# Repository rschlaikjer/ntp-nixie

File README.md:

# Nixie-NTP

### Nixie clock with NTP synchronisation

Like every amateur electrical engineer, I felt the need to make my own nixie
clock. However, I decided to add a bit of modern day tech and have the clock
set itself over NTP instead of requiring the user to manually adjust buttons.

The schematics provided detail the two boards - one control (arduino, ethernet)
and one display (shift registers, high voltage transistors).

## Partlist
#### (Digikey P/N in parens)

**Logic:**

- Atmega 328P (ATMEGA328-PU-ND / $3.01)
- Silvertel A9700 PoE module (N/A / $10)
- ENC28J60 ethernet PHY (ENC28J60-I/SO-ND / $2.83)
- RB1-125BHQ1A RJ45 jack with magnetics (N/A / $3.00)
- LM1117 3.3V regulator (LM1117T-3.3/NOPB-ND / $1.49)

**12-200V DC Boost:**
- 0.1uF 250V film cap (PCF1412CT-ND / $2.25)
- 4.7uF 450V alum cap (493-6196-1-ND / $1.51)
- MAX1771 DC-DC switching controller (MAX1771EPA+-ND / $7.23)
- 250V MOSFET (IRF644PBF-ND / $1.23)
- 100uF 20V tantalum cap (478-1746-1-ND / $2.52)
- 0.1uF 25V ceramic cap (490-1726-1-ND / $0.05)
- 10uF 25V tantalum cap (478-1762-1-ND / $1.02)
- 300V diode (ES2F-E3/52TGICT-ND / $0.40)
- 10k resistor (311-10.0KCRCT-ND / $0.02)
- 100uH inductor (M8603CT-ND / $0.81)
- 1.5M resistor (PT1.5MXCT-ND / $0.80)
- 0.05 ohm resistor (P50MCT-ND / $1.14)
- 5k trimmer pot (3214W-502ECT-ND / $3.18)

**Display Board**

- LS595 shift register with latch (296-1600-5-ND, $0.62)
- MPSA42 (or similar) high voltage transistors (MPSA42FS-ND, $0.22)
- Nixie tubes (Eagle footprint designed around the IN-14, YMMV)
- 1k resistors for regulating transistor base current
- 15k resistors for limiting nixie current

## Pretty pictures

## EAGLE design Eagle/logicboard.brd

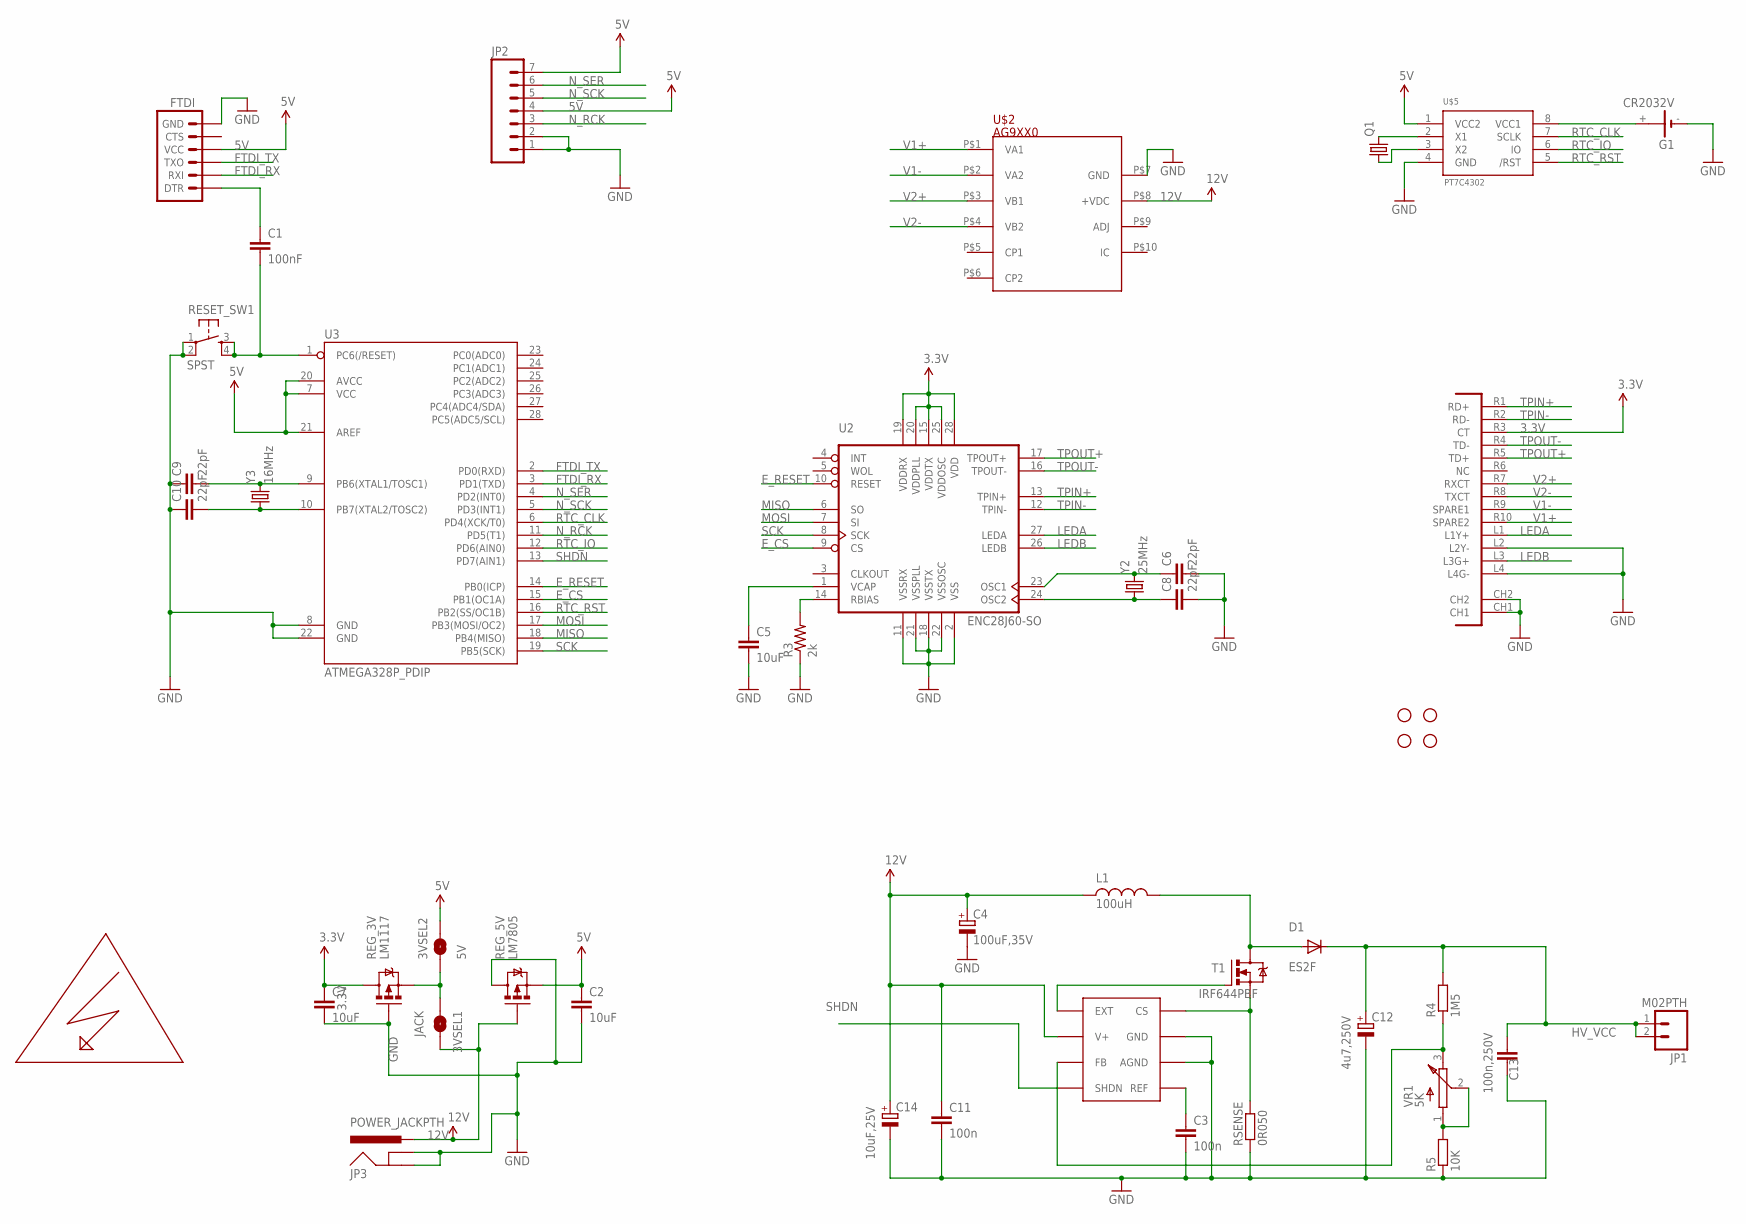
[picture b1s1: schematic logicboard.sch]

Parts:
3VSEL1: JACK; PAD-JUMPER-2-NO_YES_SILK_ROUND
3VSEL2: 5V; PAD-JUMPER-2-NO_YES_SILK_ROUND
C1: 100nF; CAP-PTH-SMALL
C2, C5, C7: 10uF; CAP-PTH-SMALL
C3, C11: 100n; C0805
C4: 100uF,35V; C-EIA-7343
C6, C8, C9, C10: 22pF; CAP-PTH-SMALL
C12: 4u7,250V; NICHICON-UJ-12
C13: 100n,250V; C2420
C14: 10uF,25V; C-EIA-7343
D1: ES2F; SMC
FTDI: ARDUINO_SERIAL_PROGRAMPTH; 1X06
G1: CR2032V
JP1: M02PTH; 1X02
JP2: M07; 1X07
JP3: POWER_JACKPTH; POWER_JACK_PTH
L1: 100uH; L-B82479
Q1: CRYSTALTC26V; TC26V
R3: 2k; AXIAL-0.1
R4: 1M5; R2512
R5: 10K; R0805
REG_3V: LM1117; TO220V
REG_5V: LM7805; TO220V
RESET_SW1: SPST; TAC-SWITCH-PTH
RSENSE: 0R050; R2010
STANDOFF1, STANDOFF2, STANDOFF3, STANDOFF4: STAND-OFF
T1: IRF644PBF; TO220BV
U2: ENC28J60-SO; SO28W
U3: ATMEGA328P_PDIP; DIL28-3
U$1: MAX1771; 8-DIP
U$2: AG9XX0; AG9000
U$3: POE-RJ45
U$4: HIGHVOLTAGE
U$5: PT7C4302; SO8
VR1: 5K; BOURNS-3214W
Y2: 25MHz; HC49US
Y3: 16MHz; HC49US

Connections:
3.3V: C7.1, REG_3V.2 (D), U2.15 (VDDTX), U2.19 (VDDRX), U2.20 (VDDPLL), U2.25 (VDDOSC), U2.28 (VDD), U$3.R3 (CT)
5V: 3VSEL2.2, C2.1, FTDI.4 (VCC), JP2.4, JP2.7, REG_5V.3 (S), U3.7 (VCC), U3.20 (AVCC), U3.21 (AREF), U$5.1 (VCC2)
12V: 3VSEL1.2, C4.+, C11.1, C14.+, JP3.PWR, L1.P$1 (1), REG_5V.1 (G), U$1.V+, U$2.P$8 (+VDC)
EXT: T1.G, U$1.EXT
E_CS: U2.9 (CS), U3.15 (PB1(OC1A))
E_RESET: U2.10 (RESET), U3.14 (PB0(ICP))
FTDI_RX: FTDI.2 (RXI), U3.3 (PD1(TXD))
FTDI_TX: FTDI.3 (TXO), U3.2 (PD0(RXD))
GND: C2.2, C3.2, C4.-, C5.2, C6.2, C7.2, C8.2, C9.1, C10.1, C11.2, C12.1 (-), C13.P$2 (2), C14.-, FTDI.6 (GND), G1.-, JP2.1, JP2.2, JP3.GND, JP3.GNDBREAK, R3.P$1 (1), R5.1, REG_3V.1 (G), REG_5V.2 (D), RESET_SW1.1, RESET_SW1.2, RSENSE.1, U2.2 (VSS), U2.11 (VSSRX), U2.18 (VSSTX), U2.21 (VSSPLL), U2.22 (VSSOSC), U3.8 (GND), U3.22 (GND), U$1.AGND, U$1.GND, U$2.P$7 (GND), U$3.CH1, U$3.CH2, U$3.L2 (L2Y-), U$3.L4 (L4G-), U$5.4 (GND)
HV_VCC: C12.2 (+), C13.P$1 (1), D1.C, JP1.1, JP1.2, R4.2
LEDA: U2.27 (LEDA), U$3.L1 (L1Y+)
LEDB: U2.26 (LEDB), U$3.L3 (L3G+)
MISO: U2.6 (SO), U3.18 (PB4(MISO))
MOSI: U2.7 (SI), U3.17 (PB3(MOSI/OC2))
unnamed: 3VSEL1.1, 3VSEL2.1, REG_3V.3 (S)
unnamed: G1.+, U$5.8 (VCC1)
unnamed: R3.P$2 (2), U2.14 (RBIAS)
unnamed: C5.1, U2.1 (VCAP)
unnamed: C6.1, U2.23 (OSC1), Y2.2
unnamed: C8.1, U2.24 (OSC2), Y2.1
unnamed: R5.2, VR1.1 (A), VR1.2 (W)
unnamed: R4.1, U$1.FB, VR1.3 (B)
unnamed: RSENSE.2, T1.S, U$1.CS
unnamed: C3.1, U$1.REF
unnamed: Q1.2, U$5.2 (X1)
unnamed: Q1.1, U$5.3 (X2)
unnamed: D1.A, L1.P$2 (2), T1.D
unnamed: C9.2, U3.9 (PB6(XTAL1/TOSC1)), Y3.2
unnamed: C10.2, U3.10 (PB7(XTAL2/TOSC2)), Y3.1
unnamed: C1.1, FTDI.1 (DTR)
N_RCK: JP2.3, U3.11 (PD5(T1))
N_SCK: JP2.5, U3.5 (PD3(INT1))
N_SER: JP2.6, U3.4 (PD2(INT0))
RESET: C1.2, RESET_SW1.3, RESET_SW1.4, U3.1 (PC6(/RESET))
RTC_CLK: U3.6 (PD4(XCK/T0)), U$5.7 (SCLK)
RTC_IO: U3.12 (PD6(AIN0)), U$5.6 (IO)
RTC_RST: U3.16 (PB2(SS/OC1B)), U$5.5 (/RST)
SCK: U2.8 (SCK), U3.19 (PB5(SCK))
SHDN: U3.13 (PD7(AIN1)), U$1.SHDN
TPIN+: U2.13 (TPIN+), U$3.R1 (RD+)
TPIN-: U2.12 (TPIN-), U$3.R2 (RD-)
TPOUT+: U2.17 (TPOUT+), U$3.R5 (TD+)
TPOUT-: U2.16 (TPOUT-), U$3.R4 (TD-)
V1+: U$2.P$1 (VA1), U$3.R10 (SPARE2)
V1-: U$2.P$2 (VA2), U$3.R9 (SPARE1)
V2+: U$2.P$3 (VB1), U$3.R7 (RXCT)
V2-: U$2.P$4 (VB2), U$3.R8 (TXCT)

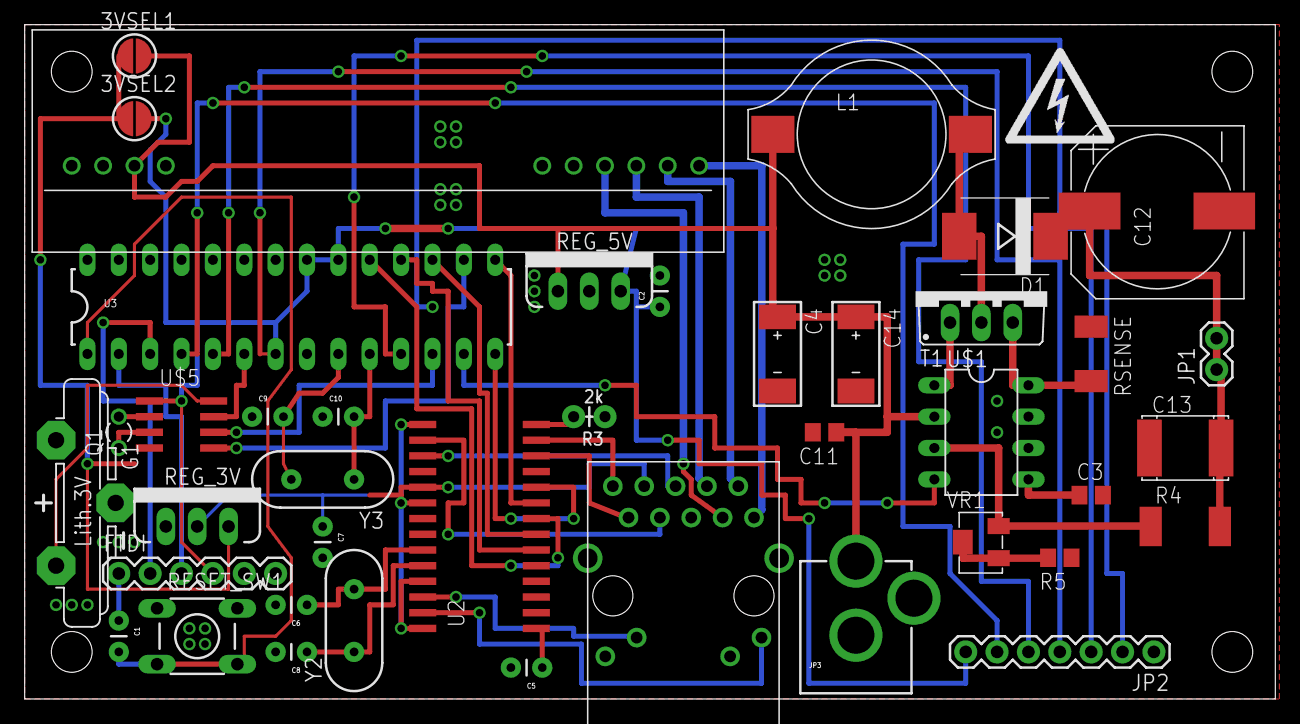
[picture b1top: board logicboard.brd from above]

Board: 2 copper layers, 101.3 x 54.6 mm, 46 parts (0 on the bottom side), 47 nets.

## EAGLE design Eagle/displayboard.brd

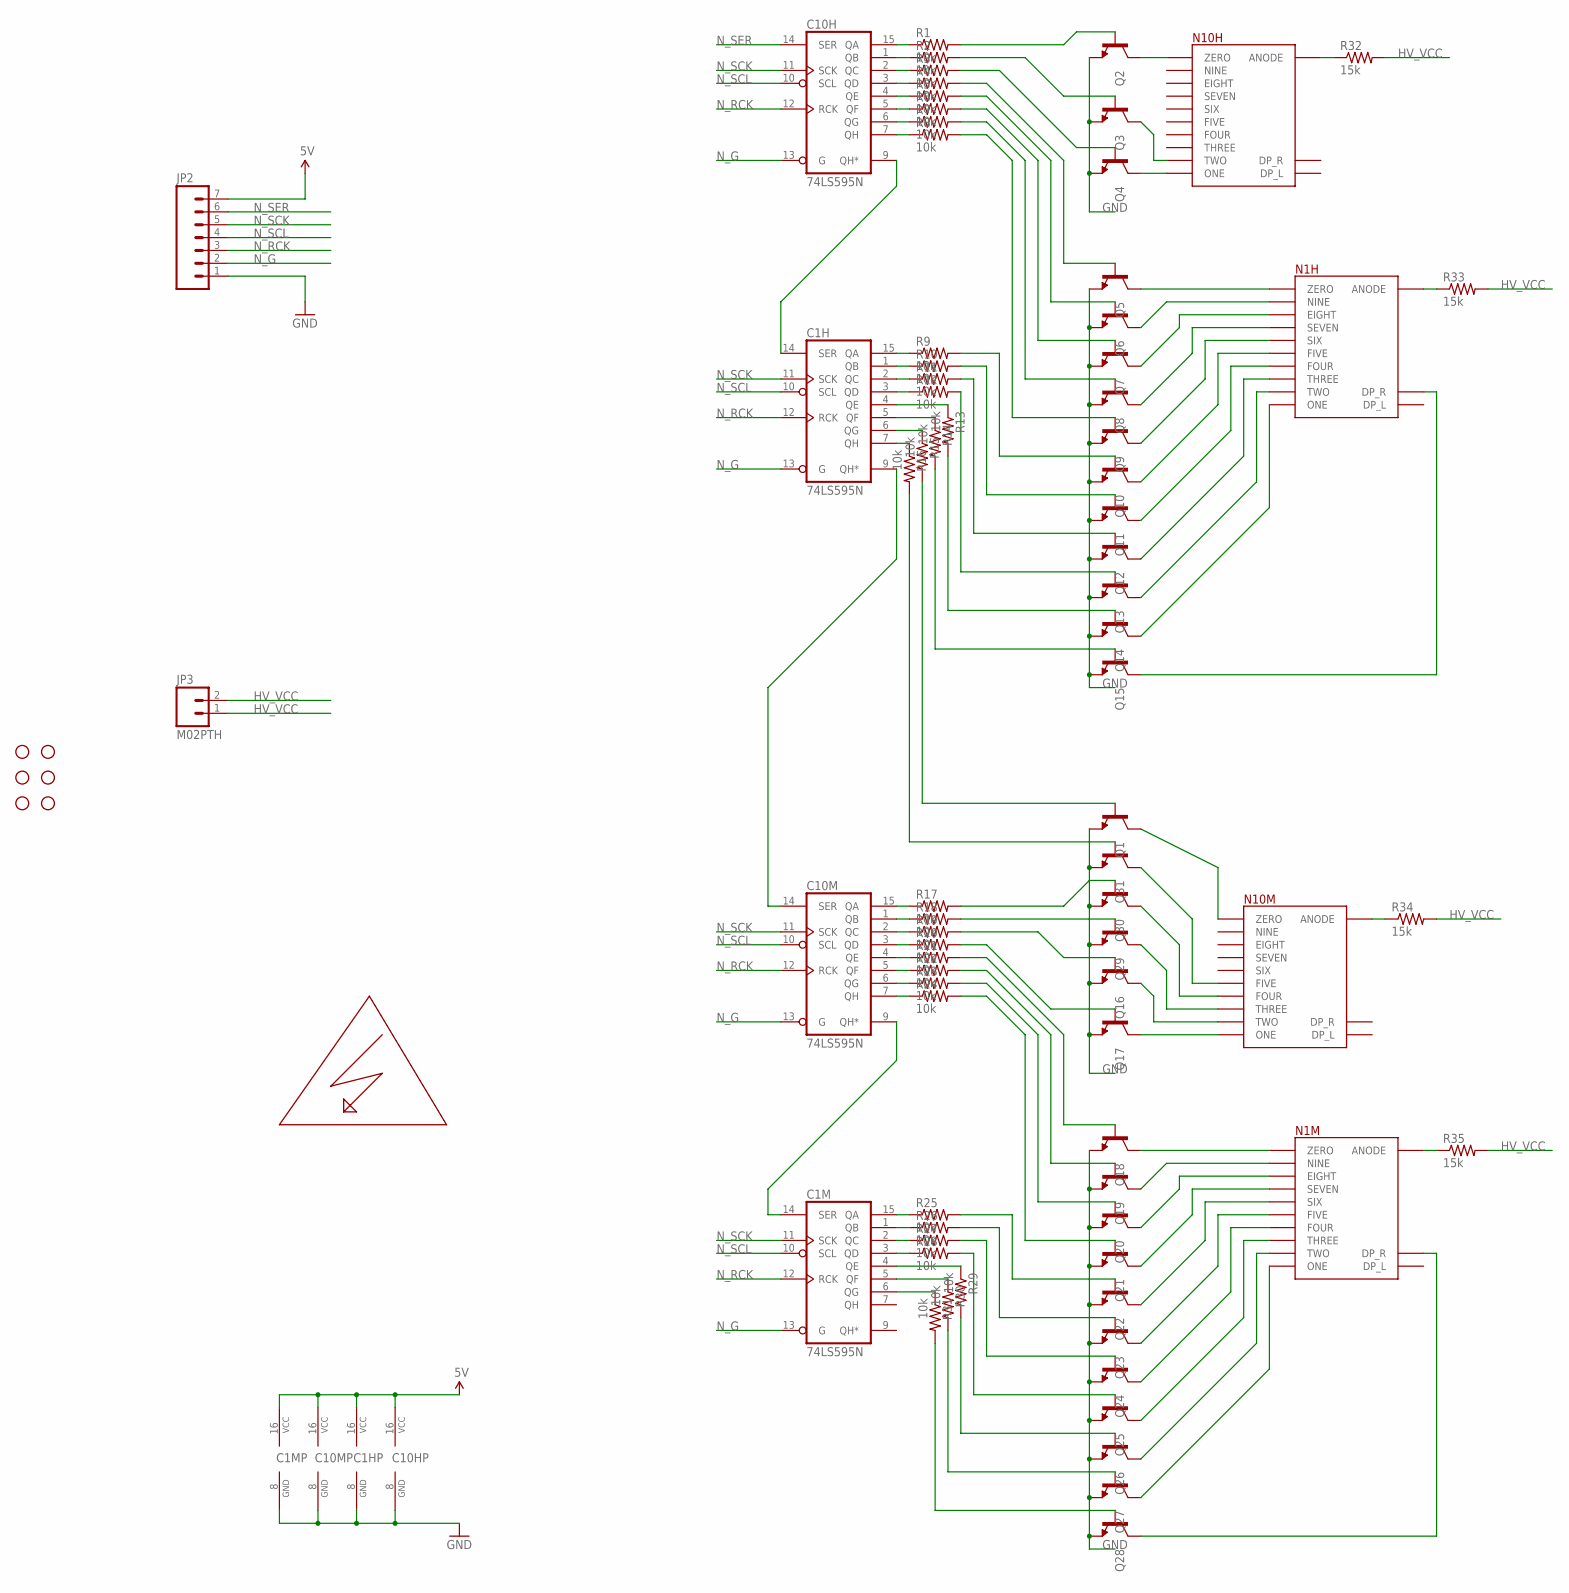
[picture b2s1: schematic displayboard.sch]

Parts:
C1H, C1M, C10H, C10M: 74LS595N; DIL16
JP2: M07; 1X07
JP3: M02PTH; 1X02
N1H, N1M, N10H, N10M: NIX13
Q1, Q2, Q3, Q4, Q5, Q6, Q7, Q8, Q9, Q10, Q11, Q12, Q13, Q14, Q15, Q16, Q17, Q18, Q19, Q20, Q21, Q22, Q23, Q24, Q25, Q26, Q27, Q28, Q29, Q30, Q31: TRANSISTOR_NPNTO92; TO-92
R1, R2, R3, R4, R5, R6, R7, R8, R9, R10, R11, R12, R13, R14, R15, R16, R17, R18, R19, R20, R21, R22, R23, R24, R25, R26, R27, R28, R29, R30, R31: 10k; 0204/7
R32, R33, R34, R35: 15k; 0207/2V
STANDOFF1, STANDOFF2, STANDOFF3, STANDOFF4, STANDOFF5, STANDOFF6: STAND-OFF
U$1: HIGHVOLTAGE

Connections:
5V: C1H.16 (VCC), C1M.16 (VCC), C10H.16 (VCC), C10M.16 (VCC), JP2.7
GND: C1H.8 (GND), C1M.8 (GND), C10H.8 (GND), C10M.8 (GND), JP2.1, Q1.1 (E), Q2.1 (E), Q3.1 (E), Q4.1 (E), Q5.1 (E), Q6.1 (E), Q7.1 (E), Q8.1 (E), Q9.1 (E), Q10.1 (E), Q11.1 (E), Q12.1 (E), Q13.1 (E), Q14.1 (E), Q15.1 (E), Q16.1 (E), Q17.1 (E), Q18.1 (E), Q19.1 (E), Q20.1 (E), Q21.1 (E), Q22.1 (E), Q23.1 (E), Q24.1 (E), Q25.1 (E), Q26.1 (E), Q27.1 (E), Q28.1 (E), Q29.1 (E), Q30.1 (E), Q31.1 (E)
HV_VCC: JP3.1, JP3.2, R32.2, R33.2, R34.2, R35.2
unnamed: N10H.ONE, Q4.3 (C)
unnamed: C10H.15 (QA), R1.1
unnamed: N10H.TWO, Q3.3 (C)
unnamed: N10H.ZERO, Q2.3 (C)
unnamed: N10M.THREE, Q29.3 (C)
unnamed: N1H.ONE, Q14.3 (C)
unnamed: N1H.TWO, Q13.3 (C)
unnamed: N1H.THREE, Q12.3 (C)
unnamed: N1H.FOUR, Q11.3 (C)
unnamed: N1H.FIVE, Q10.3 (C)
unnamed: N1H.SIX, Q9.3 (C)
unnamed: N1H.SEVEN, Q8.3 (C)
unnamed: N1H.EIGHT, Q7.3 (C)
unnamed: N1H.NINE, Q6.3 (C)
unnamed: N1H.ZERO, Q5.3 (C)
unnamed: N10M.FOUR, Q30.3 (C)
unnamed: N1H.DP_R, Q15.3 (C)
unnamed: Q2.2 (B), R1.2
unnamed: Q3.2 (B), R2.2
unnamed: C10H.1 (QB), R2.1
unnamed: C10H.2 (QC), R3.1
unnamed: Q4.2 (B), R3.2
unnamed: Q5.2 (B), R4.2
unnamed: Q6.2 (B), R5.2
unnamed: Q7.2 (B), R6.2
unnamed: Q8.2 (B), R7.2
unnamed: Q9.2 (B), R8.2
unnamed: Q10.2 (B), R9.2
unnamed: Q11.2 (B), R10.2
unnamed: Q12.2 (B), R11.2
unnamed: Q13.2 (B), R12.2
unnamed: Q14.2 (B), R13.2
unnamed: Q15.2 (B), R14.2
unnamed: N10M.ONE, Q17.3 (C)
unnamed: N10M.FIVE, Q31.3 (C)
unnamed: Q1.2 (B), R15.2
unnamed: N1M.ONE, Q27.3 (C)
unnamed: N1M.TWO, Q26.3 (C)
unnamed: N1M.THREE, Q25.3 (C)
unnamed: N1M.FOUR, Q24.3 (C)
unnamed: N1M.FIVE, Q23.3 (C)
unnamed: N1M.SIX, Q22.3 (C)
unnamed: N1M.SEVEN, Q21.3 (C)
unnamed: N1M.EIGHT, Q20.3 (C)
unnamed: N1M.NINE, Q19.3 (C)
unnamed: N1M.ZERO, Q18.3 (C)
unnamed: N10M.TWO, Q16.3 (C)
unnamed: N10M.ZERO, Q1.3 (C)
unnamed: N1M.DP_R, Q28.3 (C)
unnamed: Q30.2 (B), R17.2
unnamed: C10M.15 (QA), R17.1
unnamed: Q29.2 (B), R18.2
unnamed: C10H.3 (QD), R4.1
unnamed: C10H.4 (QE), R5.1
unnamed: C10H.5 (QF), R6.1
unnamed: C10H.6 (QG), R7.1
unnamed: Q22.2 (B), R25.2
unnamed: Q23.2 (B), R26.2
unnamed: Q24.2 (B), R27.2
unnamed: Q25.2 (B), R28.2
unnamed: Q26.2 (B), R29.2
unnamed: Q27.2 (B), R30.2
unnamed: Q28.2 (B), R31.2
unnamed: C1H.14 (SER), C10H.9 (QH*)
unnamed: C1H.9 (QH*), C10M.14 (SER)
unnamed: C1M.14 (SER), C10M.9 (QH*)
unnamed: Q31.2 (B), R16.2
unnamed: Q17.2 (B), R20.2
unnamed: Q20.2 (B), R23.2
unnamed: Q18.2 (B), R21.2
unnamed: Q19.2 (B), R22.2
unnamed: Q21.2 (B), R24.2
unnamed: C10H.7 (QH), R8.1
unnamed: C1H.15 (QA), R9.1
unnamed: C1H.2 (QC), R11.1
unnamed: C1H.1 (QB), R10.1
unnamed: C1H.3 (QD), R12.1
unnamed: C1H.4 (QE), R13.1
unnamed: C1H.5 (QF), R14.1
unnamed: C1H.6 (QG), R15.1
unnamed: C1H.7 (QH), R16.1
unnamed: C10M.1 (QB), R18.1
unnamed: C10M.2 (QC), R19.1
unnamed: C10M.3 (QD), R20.1
unnamed: C10M.4 (QE), R21.1
unnamed: C10M.5 (QF), R22.1
unnamed: C10M.6 (QG), R23.1
unnamed: C10M.7 (QH), R24.1
unnamed: Q16.2 (B), R19.2
unnamed: C1M.15 (QA), R25.1
unnamed: C1M.1 (QB), R26.1
unnamed: C1M.2 (QC), R27.1
unnamed: C1M.3 (QD), R28.1
unnamed: C1M.4 (QE), R29.1
unnamed: C1M.5 (QF), R30.1
unnamed: C1M.6 (QG), R31.1
unnamed: N10H.ANODE, R32.1
unnamed: N1M.ANODE, R35.1
unnamed: N10M.ANODE, R34.1
unnamed: N1H.ANODE, R33.1
N_G: C1H.13 (G), C1M.13 (G), C10H.13 (G), C10M.13 (G), JP2.2
N_RCK: C1H.12 (RCK), C1M.12 (RCK), C10H.12 (RCK), C10M.12 (RCK), JP2.3
N_SCK: C1H.11 (SCK), C1M.11 (SCK), C10H.11 (SCK), C10M.11 (SCK), JP2.5
N_SCL: C1H.10 (SCL), C1M.10 (SCL), C10H.10 (SCL), C10M.10 (SCL), JP2.4
N_SER: C10H.14 (SER), JP2.6

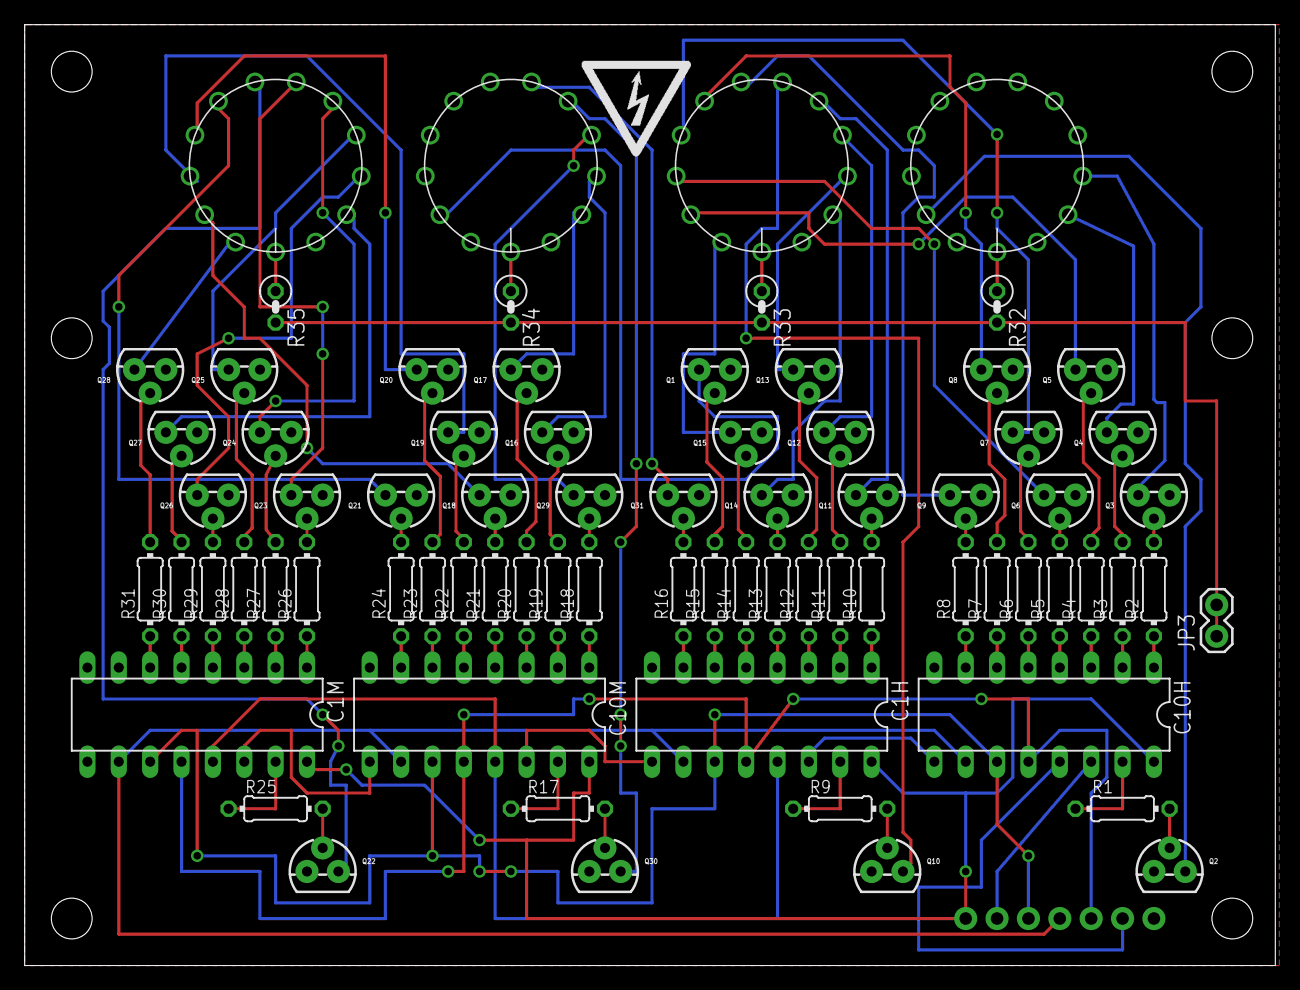
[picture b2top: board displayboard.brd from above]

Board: 2 copper layers, 101.3 x 76.2 mm, 83 parts (1 on the bottom side), 108 nets.

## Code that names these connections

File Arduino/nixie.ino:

#include <EtherCard.h>
#include <Time.h>
#include <Timezone.h>

#define N_SER 2
#define N_SCK 3
#define N_RCK 5
#define N_SCL 4
#define N_G   6

#define HV_SHDN 7

// Timezone: US East
TimeChangeRule usEDT = {"EDT", Second, Sun, Mar, 2, -240};  //UTC - 4 hours
TimeChangeRule usEST = {"EST", First, Sun, Nov, 2, -300};   //UTC - 5 hours
Timezone usEastern(usEDT, usEST);

// Ethernet
byte mac[] = {0xDE, 0xAD, 0xBE, 0xEF, 0xBA, 0xB1};
#define BUFFER_SIZE 800
byte Ethernet::buffer[BUFFER_SIZE];

// NTP
const char ntp_servname[] PROGMEM = "0.pool.ntp.org";
//uint8_t ntp_srv[] = {129,  6,   15,   29};

unsigned long millis_offset = 0;
uint8_t clientPort = 123;

// Tick scheduling
unsigned long update_interval = 1000L * 60L * 60L; // One hour
uint32_t lastUpdate = 0;
unsigned long update_display_interval = 1000L * 5L; // 5 seconds
uint32_t lastDisplayUpdate = 0;
uint32_t timeLong;

// Function prototypes
void write_595_time(uint8_t hours, uint8_t minutes, bool dp);

unsigned long getNtpTime(bool idle_anim) {
    unsigned long timeFromNTP;
    const unsigned long seventy_years = 2208988800UL;

    if (!ether.dnsLookup(ntp_servname)){
        Serial.println("DNS lookup failed");
        return 0;
    }

    ether.ntpRequest(ether.hisip, clientPort);

    int hours = 0;
    int minutes = 0;
    unsigned long idle_tick = 0;
    while(true){
        if (idle_anim && (millis() - idle_tick > 250)){
            idle_tick = millis();
            write_595_time(hours, minutes, false);
            hours = (hours + 1) % 24;
            minutes = (minutes + 1) % 60;
        }
        word length = ether.packetReceive();
        ether.packetLoop(length);
        if(length > 0 && ether.ntpProcessAnswer(&timeFromNTP, clientPort)) {
            return usEastern.toLocal(timeFromNTP - seventy_years);
        }
    }
    return 0;
}


void write_595_time(uint8_t hours, uint8_t minutes, bool dp){
    /*
       Shift register bit meanings:

    0, 1   : 10H Zero
    0, 2   : 10H Two
    0, 4   : 10H One
    0, 8   :  1H Zero
    0, 16  :  1H Nine
    0, 32  :  1H Eight
    0, 64  :  1H Seven
    0, 128 :  1H Six

    1, 1   :  1H Five
    1, 2   :  1H Four
    1, 4   :  1H Three
    1, 8   :  1H Two
    1, 16  :  1H One
    1, 32  :  1H Decimal
    1, 64  : 10M Zero
    1, 128 : 10M Five

    2, 1   : 10M Four
    2, 2   : 10M Three
    2, 4   : 10M Two
    2, 8   : 10M One
    2, 16  :  1M Zero
    2, 32  :  1M Nine
    2, 64  :  1M Eight
    2, 128 :  1M Seven

    2, 1   :  1M Six
    2, 2   :  1M Five
    2, 4   :  1M Four
    2, 8   :  1M Three
    2, 16  :  1M Two
    2, 32  :  1M One
    2, 64  :  1M Decimal
    2, 128 :  NC
    */


    uint8_t out[] = { 0, 0, 0, 0 };

    // Hour tens
    switch (hours / 10){
        case 0: out[0] |= 0x01; break;
        case 1: out[0] |= 0x04; break;
        case 2: out[0] |= 0x02; break;
    }

    // Hour ones
    switch (hours % 10){
        case 0: out[0] |= 0x08; break;
        case 9: out[0] |= 0x10; break;
        case 8: out[0] |= 0x20; break;
        case 7: out[0] |= 0x40; break;
        case 6: out[0] |= 0x80; break;
        case 5: out[1] |= 0x01; break;
        case 4: out[1] |= 0x02; break;
        case 3: out[1] |= 0x04; break;
        case 2: out[1] |= 0x08; break;
        case 1: out[1] |= 0x10; break;
    }

    // Minute tens
    switch (minutes / 10){
        case 0: out[1] |= 0x40; break;
        case 5: out[1] |= 0x80; break;
        case 4: out[2] |= 0x01; break;
        case 3: out[2] |= 0x02; break;
        case 2: out[2] |= 0x04; break;
        case 1: out[2] |= 0x08; break;
    }

    // Minute ones
    switch (minutes % 10){
        case 0: out[2] |= 0x10; break;
        case 9: out[2] |= 0x20; break;
        case 8: out[2] |= 0x40; break;
        case 7: out[2] |= 0x80; break;
        case 6: out[3] |= 0x01; break;
        case 5: out[3] |= 0x02; break;
        case 4: out[3] |= 0x04; break;
        case 3: out[3] |= 0x08; break;
        case 2: out[3] |= 0x10; break;
        case 1: out[3] |= 0x20; break;
    }

    if (dp){
        out[1] |= 0x20;
        out[3] |= 0x40;
    }

    Serial.print("Bit data: ");
    Serial.print(out[0], BIN);
    Serial.print(" ");
    Serial.print(out[1], BIN);
    Serial.print(" ");
    Serial.print(out[2], BIN);
    Serial.print(" ");
    Serial.println(out[3], BIN);

    // Output the data to the shift regs
    digitalWrite(N_RCK, LOW);
    shiftOut(N_SER, N_SCK, MSBFIRST, out[3]);
    shiftOut(N_SER, N_SCK, MSBFIRST, out[2]);
    shiftOut(N_SER, N_SCK, MSBFIRST, out[1]);
    shiftOut(N_SER, N_SCK, MSBFIRST, out[0]);
    digitalWrite(N_RCK, HIGH);
}

void print_time(){
    unsigned long time;
    time = (millis()/1000) + millis_offset;
    time = time % (60L * 60L * 24L);
    unsigned hours = (time / 60 / 60) % 24;
    unsigned minutes = (time / 60) % 60;
    unsigned seconds = time % 60;
    Serial.print(hours);
    Serial.print(":");
    Serial.print(minutes);
    Serial.print(".");
    Serial.println(seconds);
}

void update_offset(bool idle_anim){
    unsigned long time = getNtpTime(idle_anim);
    if (time){
        millis_offset = (time - (millis()/1000));
    }
}

bool dp = true;
void loop(){
    ether.packetLoop(ether.packetReceive());

    // Update the NTP offset each hour
    if(lastUpdate +  update_interval < millis()) {
        lastUpdate = millis();
        update_offset(false);
    }

    // Update the readout every ten seconds
    if (lastDisplayUpdate + update_display_interval < millis()){
        lastDisplayUpdate = millis();

        // Get the hours & minutes
        unsigned long time;
        time = (millis()/1000) + millis_offset;
        time = time % (60L * 60L * 24L);
        uint8_t hours = (time / 60 / 60) % 24;
        uint8_t minutes = (time / 60) % 60;

        // Print the time
        print_time();
        write_595_time(hours, minutes, dp);
        dp = !dp;
    }
}

void setup(){
    Serial.begin(19200);

    // HV Control pin, start with shutdown high
    pinMode(HV_SHDN, OUTPUT);
    digitalWrite(HV_SHDN, HIGH);

    // Shift register setup
    pinMode(N_SER, OUTPUT);
    pinMode(N_SCK, OUTPUT);
    pinMode(N_SCL, OUTPUT);
    pinMode(N_RCK, OUTPUT);
    pinMode(N_G, OUTPUT);
    digitalWrite(N_SCL, HIGH);
    digitalWrite(N_G, LOW);


    // Ethernet
    if (ether.begin(sizeof Ethernet::buffer, mac, 9) == 0){
        Serial.println("Couldn't init eth");
        while (1);
    }

    Serial.print("DHCP...");
    //ether.staticSetup(myip, gwip, gwip);
    //static byte dnsip[] = {8,8,8,8};
    //ether.copyIp(ether.dnsip, dnsip);
    if (!ether.dhcpSetup()){
        Serial.println(" failed.");
        while(1);
    }
    Serial.println("done.");

    lastUpdate = millis();
    Serial.println("Setup done");

    // Enable the HV system
    digitalWrite(HV_SHDN, LOW);

    // Get an initial NTP offset
    update_offset(true);
}

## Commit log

2015-04-04 Add v0 eagle files
2015-04-04 Add arduino code
2015-04-09 Don't calculate time in display code
2015-04-09 Beautify
2015-04-10 Display fixes
2015-04-27 Add controls for onboard 200V PSU
2015-04-27 Add partslist for v0.3
2015-04-27 Update schematic to include on-board 200V psu
2015-04-27 Add digi-key prices
2015-05-08 Add POST display test
2015-05-11 Flashin decimals
2015-05-11 Ensure latest eagle
2015-05-11 Use DHCP, pool NTP
2015-05-11 Update README with v3 pics
2015-05-14 Update schematics, finish RTC addition
2015-05-14 Break out schematics

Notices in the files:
parts and their libraries:
SparkFun-Connectors: Licensing: Creative Commons ShareAlike 4.0 International - https://creativecommons.org/licenses/by-sa/4.0
